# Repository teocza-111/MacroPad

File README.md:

# MacroPad
A simple keyboard with a screen and a rotary encoder.

# List of parts
1. Seeed XIAO RP2040
2. 6x MX-Style switches
3. EC11 Rotary encoder (with switch)
4. 0.91 inch OLED display
5. 6x Blank DSA keycaps
6. 4x M3x16mm screws
7. 4x M3x5mx4mm heatset inserts
8. 3D printed case

# Binds
The default bind are:
  Switches:
    -screenshot
    -copy
    -paste
    -media player previous
    -media player pause/resume
    -media player next
  Rotary encoder:
    -knob: vol up/down
    -press: mute/unmute volume

# Gallery

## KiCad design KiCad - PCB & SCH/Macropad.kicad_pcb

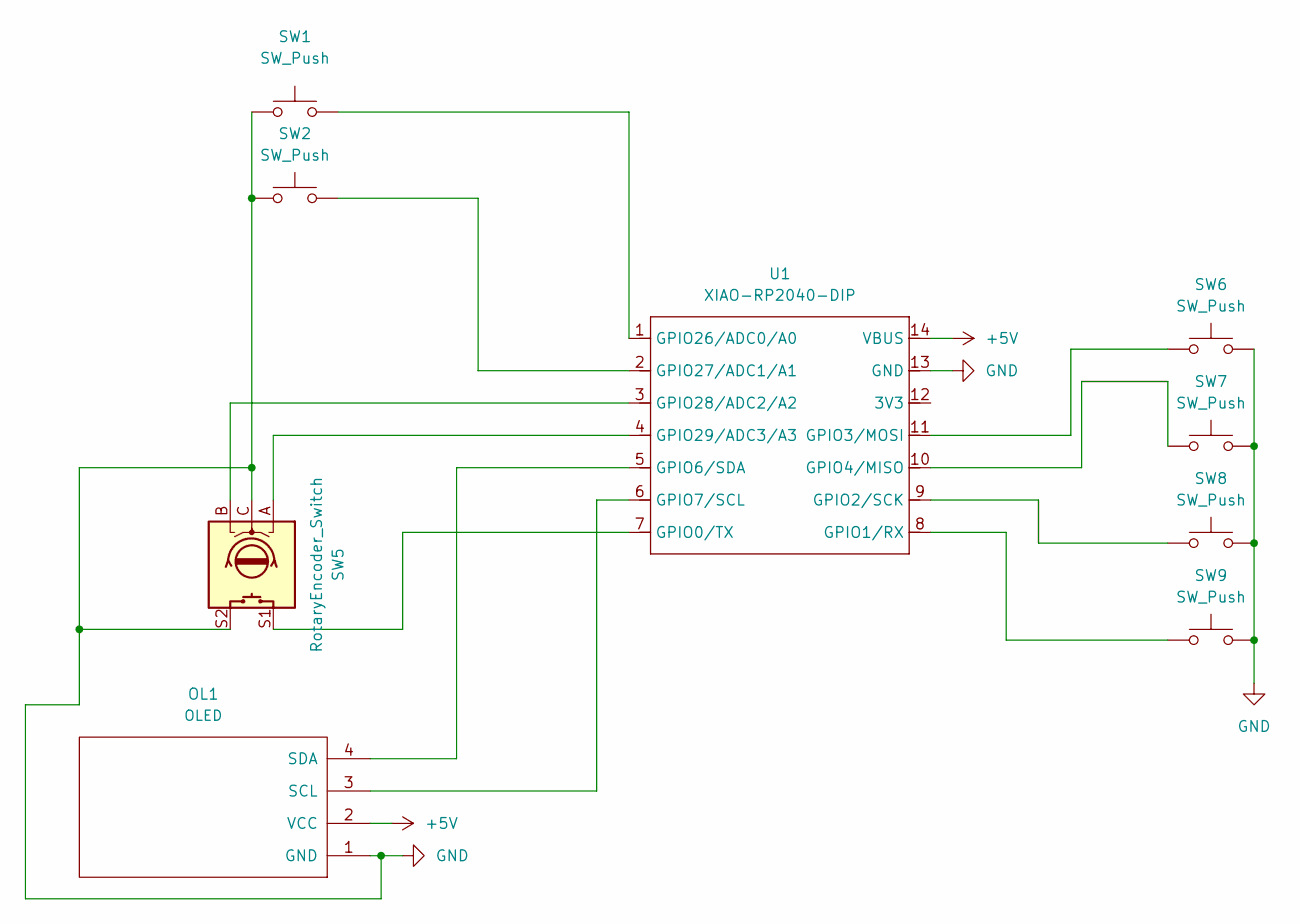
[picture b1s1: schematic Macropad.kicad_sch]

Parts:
OL1: OLED; SSD1306-0.91-OLED-4pin-128x32
SW1, SW2, SW6, SW7, SW8, SW9: SW_Push; SW_Cherry_MX_1.00u_PCB
SW5: RotaryEncoder_Switch; RotaryEncoder_Alps_EC11E-Switch_Vertical_H20mm
U1: XIAO-RP2040-DIP; XIAO-RP2040-SMD

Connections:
+5V: OL1.2 (VCC), U1.14 (VBUS)
GND: OL1.1 (GND), SW1.2, SW2.1, SW5.C, SW5.S2, SW6.2, SW7.2, SW8.2, SW9.2, U1.13 (GND)
unnamed: OL1.3 (SCL), U1.6 (GPIO7/SCL)
unnamed: OL1.4 (SDA), U1.5 (GPIO6/SDA)
unnamed: SW5.S1, U1.7 (GPIO0/TX)
unnamed: SW9.1, U1.8 (GPIO1/RX)
unnamed: SW8.1, U1.9 (GPIO2/SCK)
unnamed: SW6.1, U1.11 (GPIO3/MOSI)
unnamed: SW7.1, U1.10 (GPIO4/MISO)
unnamed: SW1.1, U1.1 (GPIO26/ADC0/A0)
unnamed: SW2.2, U1.2 (GPIO27/ADC1/A1)
unnamed: SW5.B, U1.3 (GPIO28/ADC2/A2)
unnamed: SW5.A, U1.4 (GPIO29/ADC3/A3)

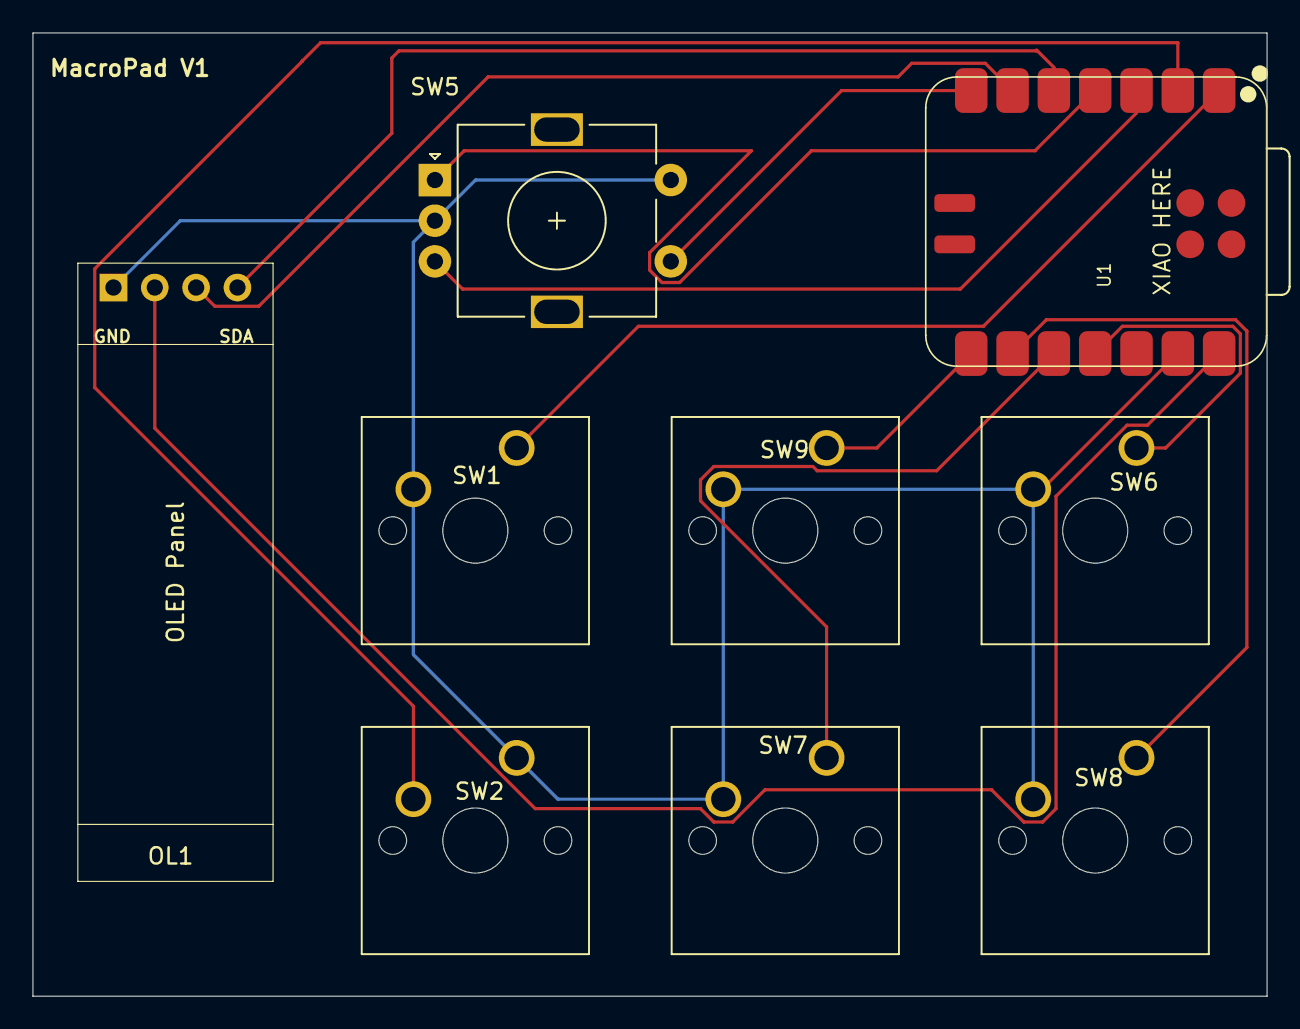
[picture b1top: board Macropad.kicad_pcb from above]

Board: 2 copper layers, 75.9 x 59.2 mm, 9 parts (0 on the bottom side), 13 nets.

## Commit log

2025-12-22 Add parts list to README.md
    Added a list of parts required for the MacroPad.
2025-12-22 Update README.md
    Added a gallery section with image links.
2025-12-23 Added the bill of materials
